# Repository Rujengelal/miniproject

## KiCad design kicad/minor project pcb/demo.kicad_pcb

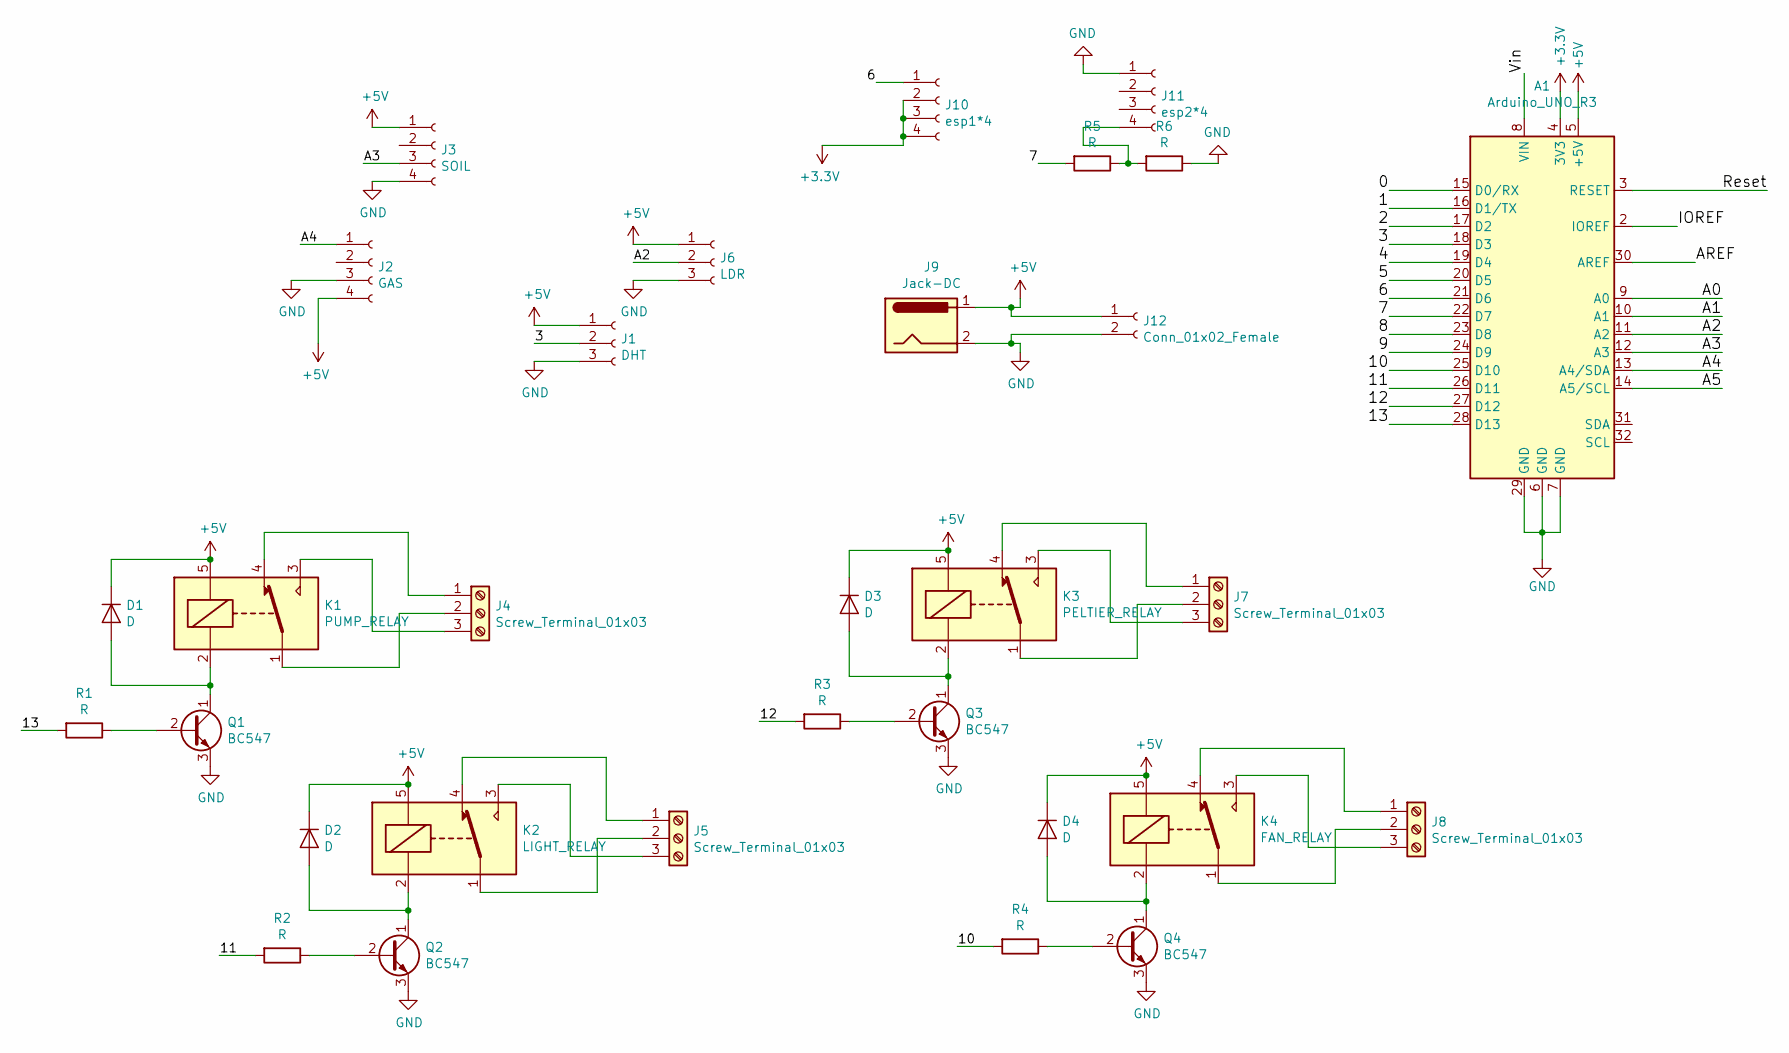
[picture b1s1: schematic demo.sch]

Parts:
A1: Arduino_UNO_R3
D1, D2, D3, D4: D; D_5KP_P10.16mm_Horizontal
J1: DHT; PinSocket_1x03_P2.00mm_Vertical
J2: GAS; PinSocket_1x04_P2.00mm_Vertical
J3: SOIL; PinSocket_1x04_P2.00mm_Vertical
J4, J5, J7, J8: Screw_Terminal_01x03; TerminalBlock_bornier-3_P5.08mm
J6: LDR; PinSocket_1x03_P2.00mm_Vertical
J9: Jack-DC; BarrelJack_Horizontal
J10: esp1*4; PinSocket_1x04_P2.00mm_Vertical
J11: esp2*4; PinSocket_1x04_P2.00mm_Vertical
J12: Conn_01x02_Female; PinSocket_1x02_P2.00mm_Vertical
K1: PUMP_RELAY; Relay_SPDT_SANYOU_SRD_Series_Form_C
K2: LIGHT_RELAY; Relay_SPDT_SANYOU_SRD_Series_Form_C
K3: PELTIER_RELAY; Relay_SPDT_SANYOU_SRD_Series_Form_C
K4: FAN_RELAY; Relay_SPDT_SANYOU_SRD_Series_Form_C
Q1, Q2, Q3, Q4: BC547; TO-92L_Wide
R1, R2, R3, R4, R5, R6: R; R_Axial_DIN0204_L3.6mm_D1.6mm_P5.08mm_Horizontal

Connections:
+3V3: A1.4 (3V3), J10.2, J10.3, J10.4
+5V: A1.5 (+5V), D1.1 (K), D2.1 (K), D3.1 (K), D4.1 (K), J1.1, J2.4, J3.1, J6.1, J9.1, J12.1, K1.5, K2.5, K3.5, K4.5
/0: A1.15 (D0/RX)
/1: A1.16 (D1/TX)
/2: A1.17 (D2)
/3: A1.18 (D3), J1.2
/4: A1.19 (D4)
/5: A1.20 (D5)
/6: A1.21 (D6), J10.1
/7: A1.22 (D7), R5.2
/8: A1.23 (D8)
/9: A1.24 (D9)
/10: A1.25 (D10), R4.2
/11: A1.26 (D11), R2.2
/12: A1.27 (D12), R3.2
/13: A1.28 (D13), R1.2
/A0: A1.9 (A0)
/A1: A1.10 (A1)
/A2: A1.11 (A2), J6.2
/A3: A1.12 (A3), J3.3
/A4: A1.13 (A4/SDA), J2.1
/A5: A1.14 (A5/SCL)
/AREF: A1.30 (AREF)
/IOREF: A1.2 (IOREF)
/Reset: A1.3 (RESET)
/Vin: A1.8 (VIN)
GND: A1.6 (GND), A1.7 (GND), A1.29 (GND), J1.3, J2.3, J3.4, J6.3, J9.2, J11.1, J12.2, Q1.3 (E), Q2.3 (E), Q3.3 (E), Q4.3 (E), R6.1
unnamed: D1.2 (A), K1.2, Q1.1 (C)
unnamed: D2.2 (A), K2.2, Q2.1 (C)
unnamed: D3.2 (A), K3.2, Q3.1 (C)
unnamed: D4.2 (A), K4.2, Q4.1 (C)
unnamed: J4.1, K1.4
unnamed: J4.2, K1.1
unnamed: J4.3, K1.3
unnamed: J5.1, K2.4
unnamed: J5.2, K2.1
unnamed: J5.3, K2.3
unnamed: J7.1, K3.4
unnamed: J7.2, K3.1
unnamed: J7.3, K3.3
unnamed: J8.1, K4.4
unnamed: J8.2, K4.1
unnamed: J8.3, K4.3
unnamed: J11.4, R5.1, R6.2
unnamed: Q1.2 (B), R1.1
unnamed: Q2.2 (B), R2.1
unnamed: Q3.2 (B), R3.1
unnamed: Q4.2 (B), R4.1

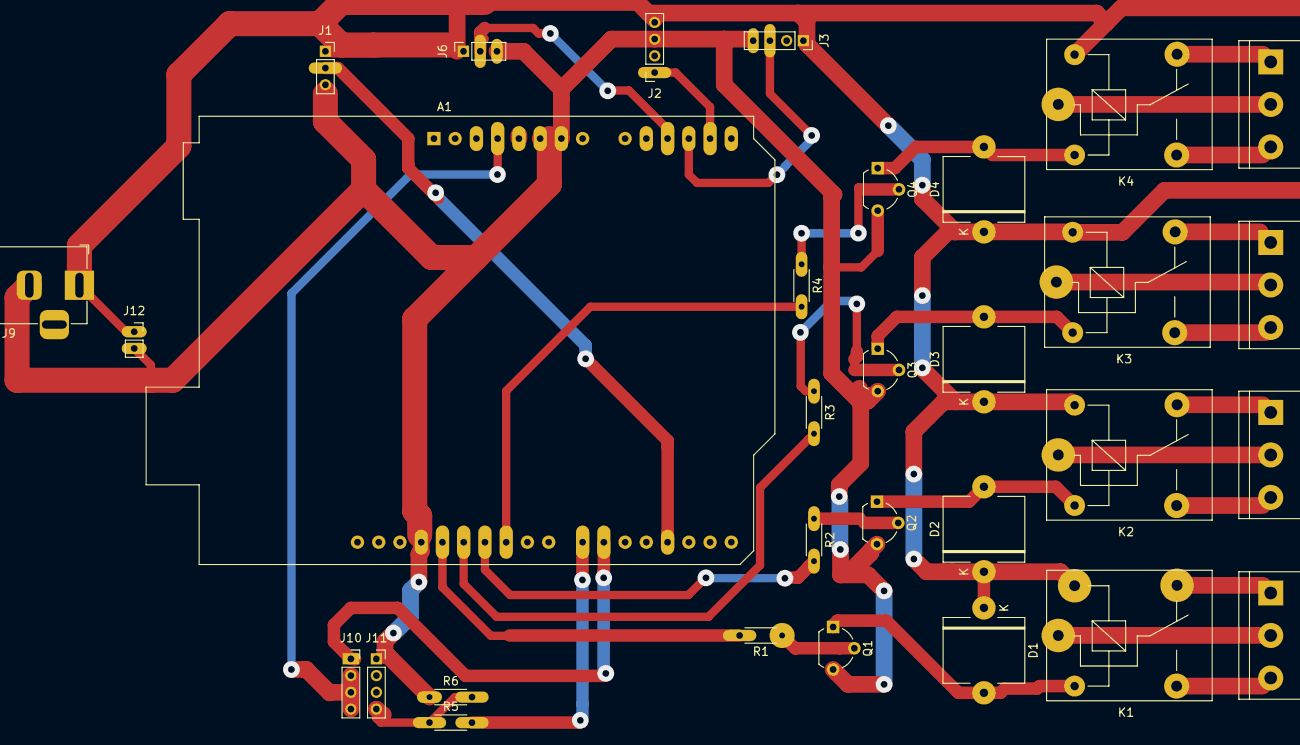
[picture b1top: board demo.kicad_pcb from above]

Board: 2 copper layers, 31 parts (0 on the bottom side), 34 nets.

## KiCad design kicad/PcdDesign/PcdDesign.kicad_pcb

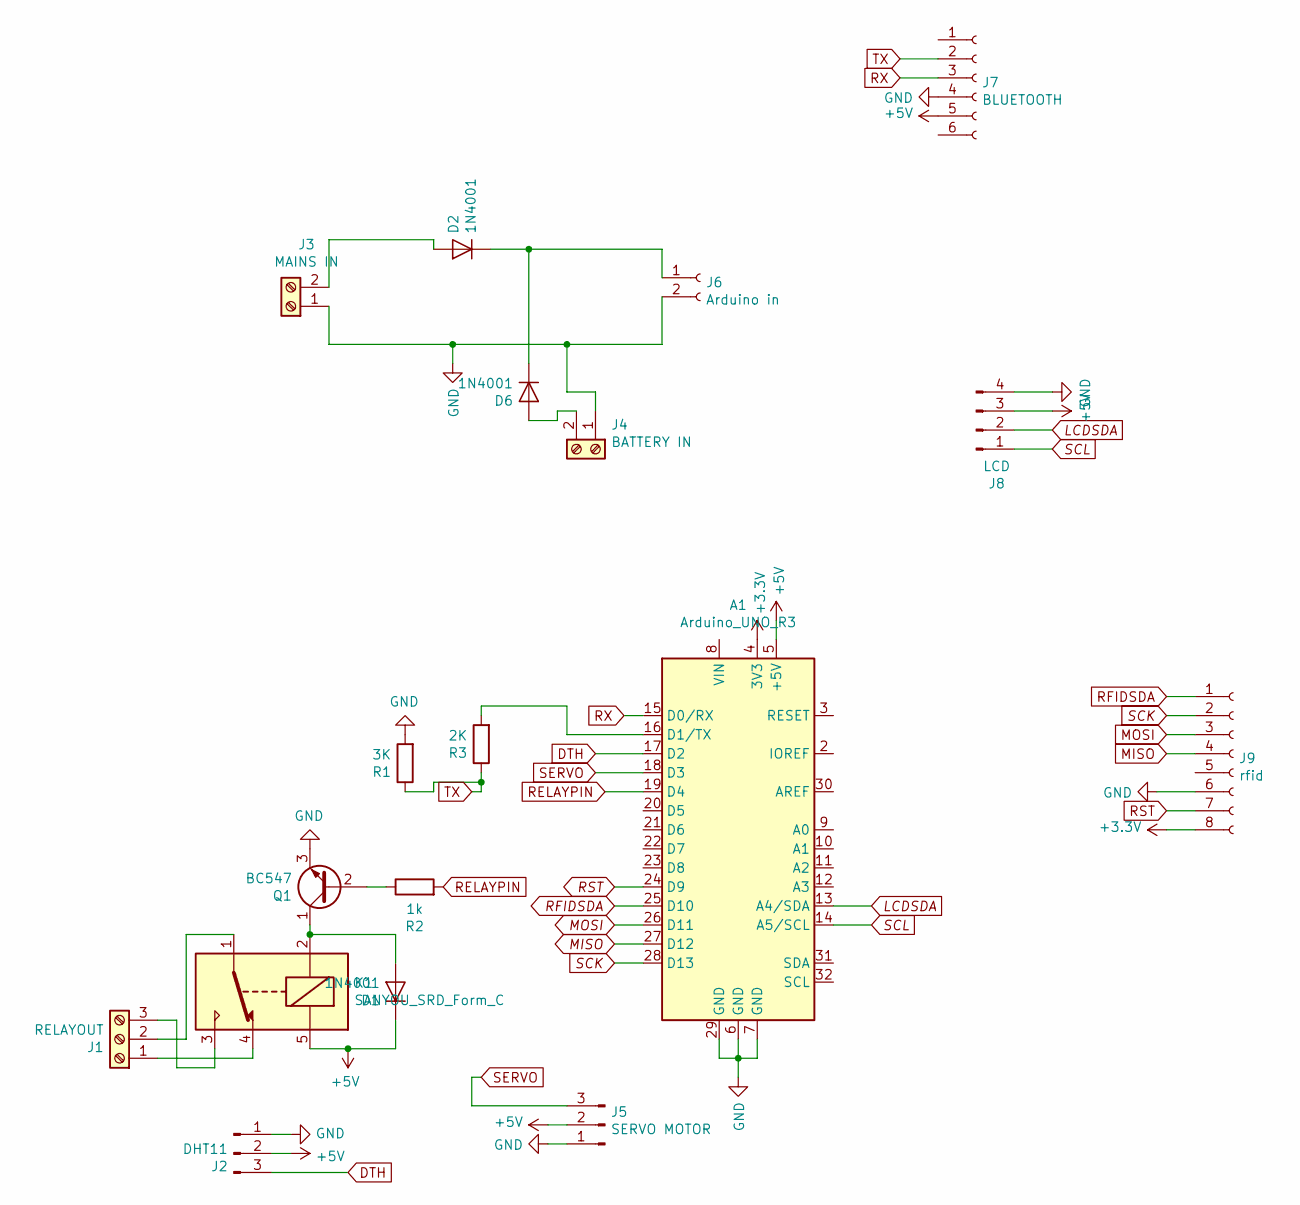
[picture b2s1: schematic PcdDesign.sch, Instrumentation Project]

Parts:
A1: Arduino_UNO_R3
D1, D2, D6: 1N4001; D_DO-41_SOD81_P10.16mm_Horizontal
J1: RELAYOUT; TerminalBlock_bornier-3_P5.08mm
J2: DHT11; PinSocket_1x03_P2.54mm_Vertical
J3: MAINS IN; TerminalBlock_bornier-2_P5.08mm
J4: BATTERY IN; TerminalBlock_bornier-2_P5.08mm
J5: SERVO MOTOR; PinHeader_1x03_P2.54mm_Vertical
J6: Arduino in; PinHeader_1x02_P2.54mm_Vertical
J7: BLUETOOTH; PinSocket_1x06_P2.54mm_Horizontal
J8: LCD; PinSocket_1x04_P2.54mm_Horizontal
J9: rfid; PinSocket_1x08_P2.54mm_Vertical
K1: SANYOU_SRD_Form_C; Relay_SPDT_SANYOU_SRD_Series_Form_C
Q1: BC547; TO-92_Inline_Wide
R1: 3K; R_Axial_DIN0207_L6.3mm_D2.5mm_P7.62mm_Horizontal
R2: 1k; R_Axial_DIN0207_L6.3mm_D2.5mm_P7.62mm_Horizontal
R3: 2K; R_Axial_DIN0207_L6.3mm_D2.5mm_P7.62mm_Horizontal

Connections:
+3V3: A1.4 (3V3), J9.8
+5V: A1.5 (+5V), D1.1 (K), J2.2, J5.2, J7.5, J8.3, K1.5
DTH: A1.17 (D2), J2.3
GND: A1.6 (GND), A1.7 (GND), A1.29 (GND), J2.1, J3.1, J4.1, J5.1, J6.2, J7.4, J8.4, J9.6, Q1.3 (E), R1.2
LCDSDA: A1.13 (A4/SDA), J8.2
MISO: A1.27 (D12), J9.4
MOSI: A1.26 (D11), J9.3
unnamed: A1.16 (D1/TX), R3.2
unnamed: D1.2 (A), K1.2, Q1.1 (C)
unnamed: D2.1 (K), D6.1 (K), J6.1
unnamed: D2.2 (A), J3.2
unnamed: D6.2 (A), J4.2
unnamed: J1.1, K1.4
unnamed: J1.2, K1.1
unnamed: J1.3, K1.3
unnamed: Q1.2 (B), R2.1
RELAYPIN: A1.19 (D4), R2.2
RFIDSDA: A1.25 (D10), J9.1
RST: A1.24 (D9), J9.7
RX: A1.15 (D0/RX), J7.3
SCK: A1.28 (D13), J9.2
SCL: A1.14 (A5/SCL), J8.1
SERVO: A1.18 (D3), J5.3
TX: J7.2, R1.1, R3.1

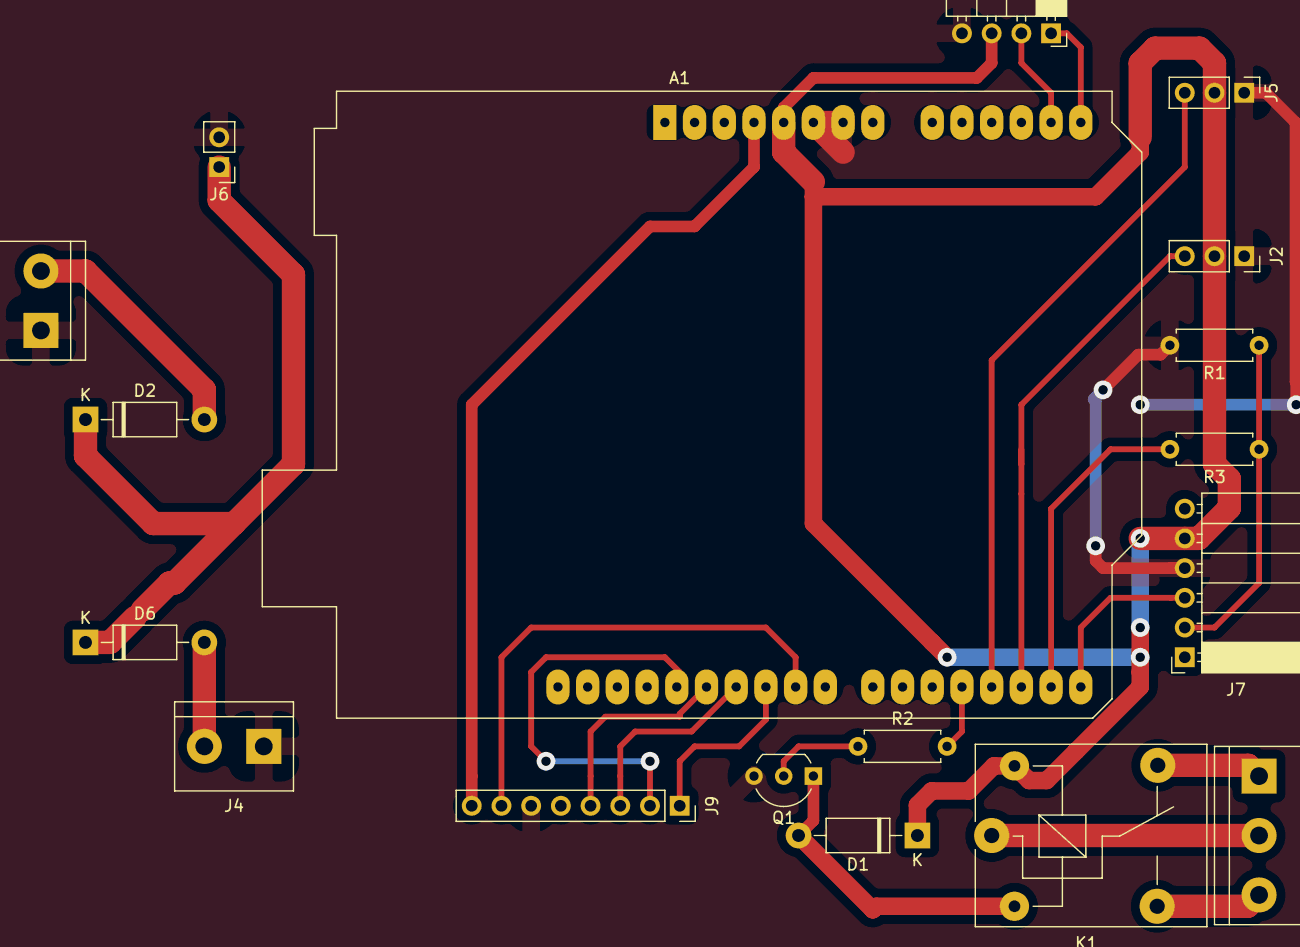
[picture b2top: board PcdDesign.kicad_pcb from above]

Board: 2 copper layers, 18 parts (0 on the bottom side), 24 nets.

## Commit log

2020-12-04 2020/12/4
